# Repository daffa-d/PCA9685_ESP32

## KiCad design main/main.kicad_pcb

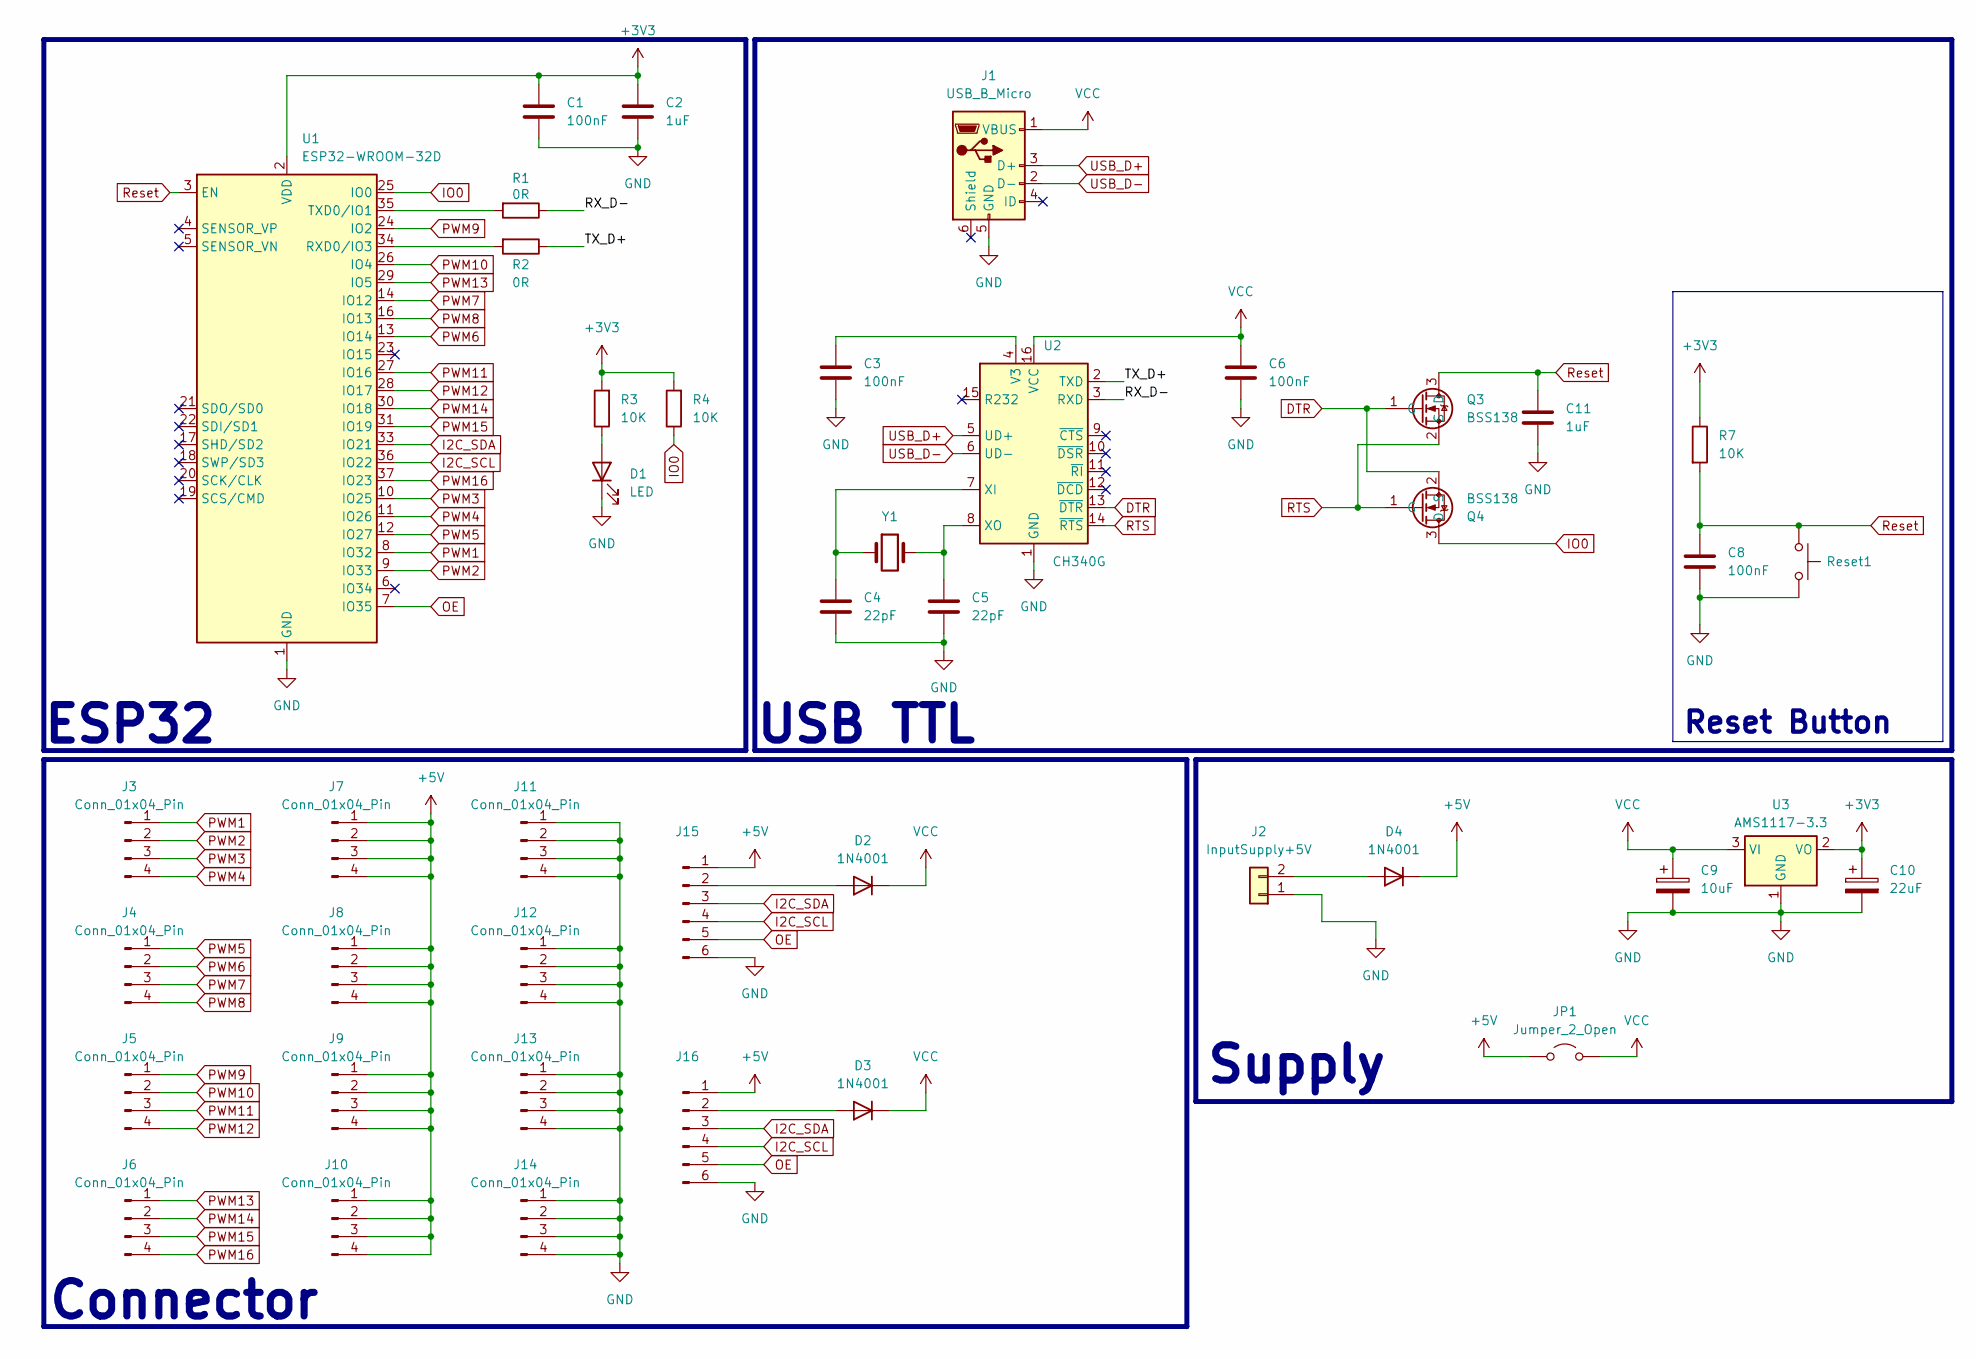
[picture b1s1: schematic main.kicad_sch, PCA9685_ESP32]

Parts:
C1, C3, C6, C8: 100nF; C_0805_2012Metric_Pad1.18x1.45mm_HandSolder
C2, C11: 1uF; C_0805_2012Metric_Pad1.18x1.45mm_HandSolder
C4, C5: 22pF; C_0805_2012Metric_Pad1.18x1.45mm_HandSolder
C9: 10uF; C_Radial_D5.0mm_H11.0mm_P2.00mm
C10: 22uF; C_Radial_D5.0mm_H11.0mm_P2.00mm
D1: LED; LED_0805_2012Metric_Pad1.15x1.40mm_HandSolder
D2, D3, D4: 1N4001; D_SMA_Handsoldering
J1: USB_B_Micro; USB_Micro-B_Amphenol_10103594-0001LF_Horizontal
J2: InputSupply+5V; TerminalBlock_Phoenix_MKDS-1,5-2-5.08_1x02_P5.08mm_Horizont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
J3, J4, J5, J6, J7, J8, J9, J10, J11, J12, J13, J14: Conn_01x04_Pin; PinHeader_1x04_P2.54mm_Vertical
J15, J16: Conn_01x06_Pin; PinHeader_1x06_P2.54mm_Vertical
JP1: Jumper_2_Open; SolderJumper-2_P1.3mm_Open_TrianglePad1.0x1.5mm
Q3, Q4: BSS138; SOT-23
R1, R2: 0R; R_0805_2012Metric_Pad1.20x1.40mm_HandSolder
R3, R4, R7: 10K; R_0805_2012Metric_Pad1.20x1.40mm_HandSolder
Reset1: SW_Push; SW_PUSH_6mm
U1: ESP32-WROOM-32D; ESP32-WROOM-32
U2: CH340G; SOIC-16_3.9x9.9mm_P1.27mm
U3: AMS1117-3.3; SOT-223-3_TabPin2
Y1: Crystal; Crystal_SMD_HC49-SD

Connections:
+3V3: C1.1, C2.1, C10.1, R3.2, R4.2, R7.1, U1.2 (VDD), U3.2 (VO)
+5V: D4.1 (K), J7.1, J7.2, J7.3, J7.4, J8.1, J8.2, J8.3, J8.4, J9.1, J9.2, J9.3, J9.4, J10.1, J10.2, J10.3, J10.4, J15.1, J16.1, JP1.1 (A)
/RX_D-: R1.1, U2.3 (RXD)
/TX_D+: R2.1, U2.2 (TXD)
DTR: Q3.1 (G), Q4.2 (S), U2.13 (~DTR); also elsewhere on the board
GND: C1.2, C2.2, C3.2, C4.2, C5.2, C6.2, C8.2, C9.2, C10.2, C11.2, D1.1 (K), J1.5 (GND), J2.1, J11.1, J11.2, J11.3, J11.4, J12.1, J12.2, J12.3, J12.4, J13.1, J13.2, J13.3, J13.4, J14.1, J14.2, J14.3, J14.4, J15.6, J16.6, Reset1.2, U1.1 (GND), U1.15 (GND), U1.38 (GND), U1.39 (GND), U2.1 (GND), U3.1 (GND)
I2C_SCL: J15.4, J16.4, U1.36 (IO22)
I2C_SDA: J15.3, J16.3, U1.33 (IO21)
IO0: Q4.3 (D), R4.1, U1.25 (IO0); also elsewhere on the board
unnamed: D1.2 (A), R3.1
unnamed: D2.2 (A), J15.2
unnamed: D3.2 (A), J16.2
unnamed: D4.2 (A), J2.2
unnamed: R2.2, U1.34 (RXD0/IO3)
unnamed: R1.2, U1.35 (TXD0/IO1)
unnamed: C3.1, U2.4 (V3)
unnamed: C4.1, U2.7 (XI), Y1.1
unnamed: C5.1, U2.8 (XO), Y1.2
OE: J15.5, J16.5, U1.7 (IO35)
PWM1: J3.1, U1.8 (IO32)
PWM2: J3.2, U1.9 (IO33)
PWM3: J3.3, U1.10 (IO25)
PWM4: J3.4, U1.11 (IO26)
PWM5: J4.1, U1.12 (IO27)
PWM6: J4.2, U1.13 (IO14)
PWM7: J4.3, U1.14 (IO12)
PWM8: J4.4, U1.16 (IO13)
PWM9: J5.1, U1.24 (IO2)
PWM10: J5.2, U1.26 (IO4)
PWM11: J5.3, U1.27 (IO16)
PWM12: J5.4, U1.28 (IO17)
PWM13: J6.1, U1.29 (IO5)
PWM14: J6.2, U1.30 (IO18)
PWM15: J6.3, U1.31 (IO19)
PWM16: J6.4, U1.37 (IO23)
RTS: Q3.2 (S), Q4.1 (G), U2.14 (~RTS); also elsewhere on the board
Reset: C8.1, C11.1, Q3.3 (D), R7.2, Reset1.1, U1.3 (EN); also elsewhere on the board
USB_D+: J1.3 (D+), U2.5 (UD+)
USB_D-: J1.2 (D-), U2.6 (UD-)
VCC: C6.1, C9.1, D2.1 (K), D3.1 (K), J1.1 (VBUS), JP1.2 (B), U2.16 (VCC), U3.3 (VI)

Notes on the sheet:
Connector
Reset Button
ESP32
USB TTL
Supply

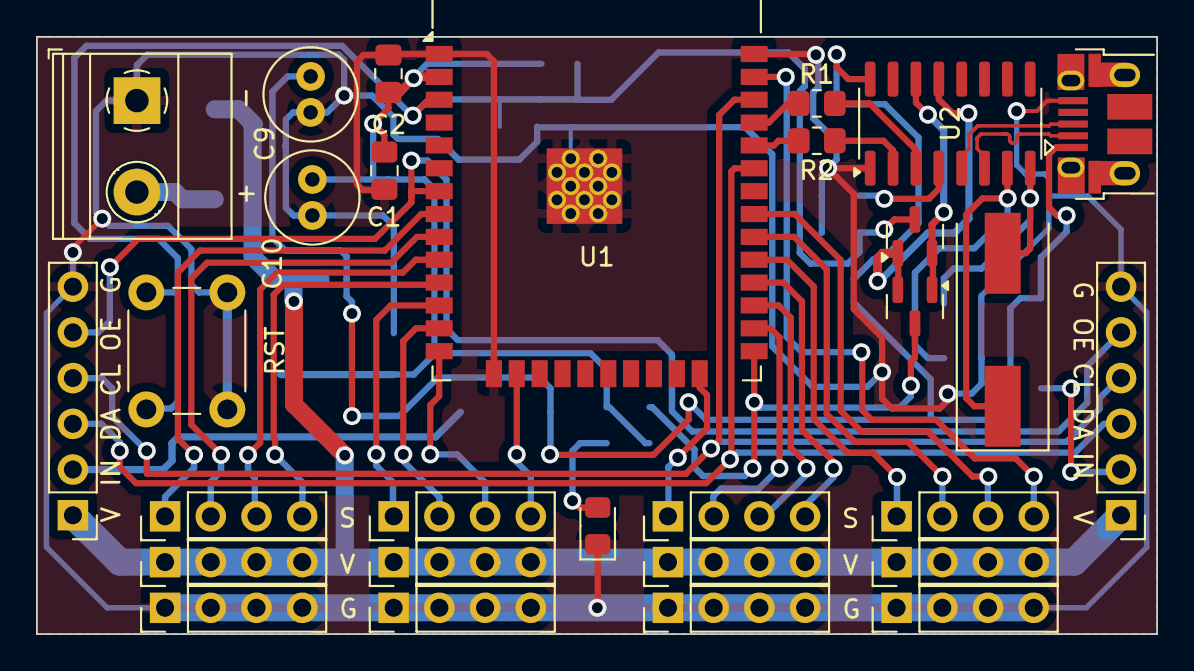
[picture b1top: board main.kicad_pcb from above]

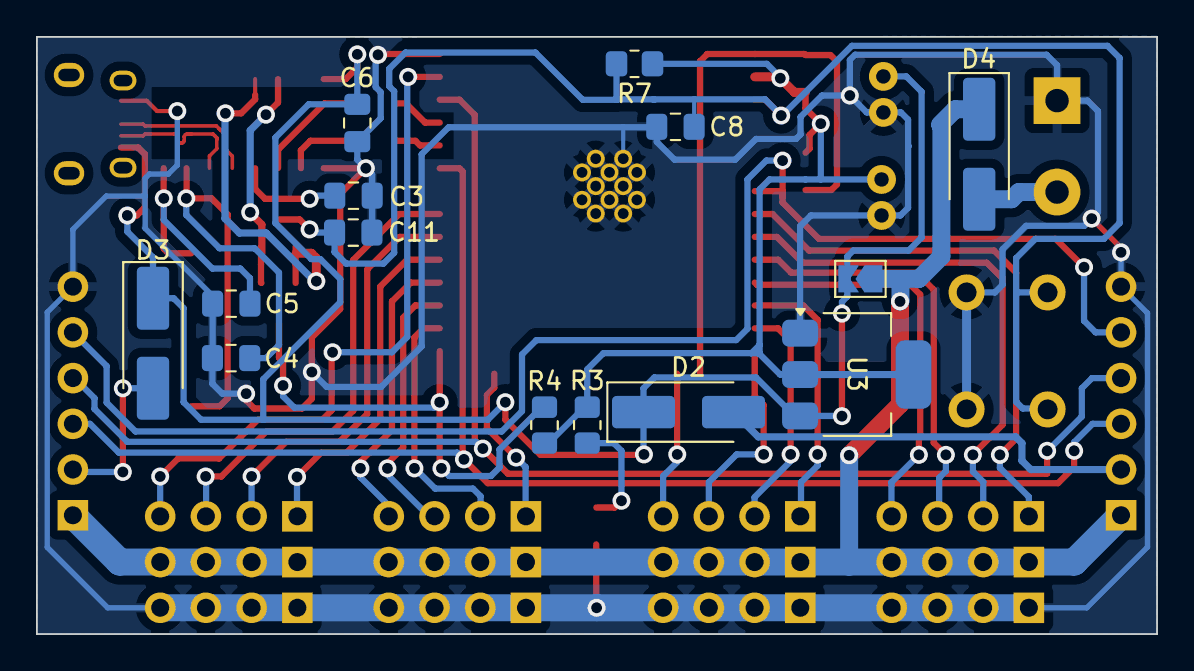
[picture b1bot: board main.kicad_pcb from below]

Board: 2 copper layers, 62.2 x 33.2 mm, 43 parts (14 on the bottom side), 40 nets.

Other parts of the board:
Q1, Q2: BSS138; SOT-23

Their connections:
DTR: Q1.1 (G), Q2.2 (S); also elsewhere on the board
IO0: Q2.3 (D); also elsewhere on the board
RTS: Q1.2 (S), Q2.1 (G); also elsewhere on the board
Reset: Q1.3 (D); also elsewhere on the board

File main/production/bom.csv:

Designator,Footprint,Quantity,Value,LCSC Part #
"C1, C3, C6, C8",0805,4,100nF,
C10,C_Radial_D5.0mm_H11.0mm_P2.00mm,1,22uF,
"C11, C2",0805,2,1uF,
"C4, C5",0805,2,22pF,
C9,C_Radial_D5.0mm_H11.0mm_P2.00mm,1,10uF,
D1,0805,1,LED,
"D2, D3, D4",D_SMA_Handsoldering,3,1N4001,
J1,USB_Micro-B_Amphenol_10103594-0001LF_Horizontal,1,USB_B_Micro,
"J10, J11, J12, J13, J14, J3, J4, J5, J6, J7, J8, J9",PinHeader_1x04_P2.54mm_Vertical,12,Conn_01x04_Pin,
"J15, J16",PinHeader_1x06_P2.54mm_Vertical,2,Conn_01x06_Pin,
J2,"TerminalBlock_Phoenix_MKDS-1,5-2-5.08_1x02_P5.08mm_Horizontal",1,InputSupply+5V,
JP1,SolderJumper-2_P1.3mm_Open_TrianglePad1.0x1.5mm,1,Jumper_2_Open,
"Q1, Q2",SOT-23,2,BSS138,
"R1, R2",0805,2,0R,
"R3, R4, R7",0805,3,10K,
RESET1,SW_PUSH_6mm,1,SW_Push,
U1,ESP32-WROOM-32,1,ESP32-WROOM-32D,
U2,SOIC-16_3.9x9.9mm_P1.27mm,1,CH340G,
U3,SOT-223-3_TabPin2,1,AMS1117-3.3,
Y1,Crystal_SMD_HC49-SD,1,Crystal,

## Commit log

2025-03-05 first Push
